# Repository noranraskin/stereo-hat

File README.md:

# Smart Stereo

A small, power-efficient AirPlay 2 network amplifier. A custom stereo class-D amplifier HAT sits on a Radxa Zero 3E running NixOS and `shairport-sync`, so any Apple device (or anything that speaks AirPlay 2) can stream straight to a pair of passive speakers over Ethernet.

## How it works

```
 iPhone / Mac ──AirPlay 2──▶ Ethernet ──▶ Radxa Zero 3E (NixOS, shairport-sync)
                                              │  I2S (pins 12, 35, 38, 40)
                                              │  I2C (pins 3, 5)
                                              ▼
 12–24 V DC ──▶ HAT ──▶ TPS54232 buck ──5 V──▶ SBC (via header pins 2/4)
                 │                      SBC 3.3 V ──▶ TAS5756M logic
                 └──────────── VIN ───▶ TAS5756M power stage ──▶ L / R speakers
```

- **SBC:** [Radxa Zero 3E](https://radxa.com/products/zeros/zero3e/). Small, low power, and has wired Ethernet. Any SBC with a Raspberry Pi-style 40-pin header and an I2S interface on the standard pins should work.
- **Amplifier:** TI [TAS5756M](https://www.ti.com/product/TAS5756M), a stereo I2S-input class-D amp with a built-in DAC and DSP. It receives audio over I2S and is configured over I2C.
- **Power:** one 12–24 V DC input feeds the amplifier directly. A TI [TPS54232](https://www.ti.com/product/TPS54232) buck converter makes 5 V for the SBC, so you need only one power supply. The 3.3 V for the amplifier's logic comes back from the SBC's own regulator.
- **Software:** NixOS, configured declaratively, so the same config can be copied to any number of speakers. `shairport-sync` is built with AirPlay 2 support, and `nqptp` handles AirPlay 2 timing.

The HAT is pin-compatible with the [HiFiBerry Amp2](https://www.hifiberry.com/shop/boards/hifiberry-amp2/), so it also works on a Raspberry Pi with the HiFiBerry drivers.

> [!IMPORTANT] 
> **!!IMPORTANT!! USING A SELF ASSEMBLED HAT WITH A RADXA AND NIXOS IS SOMEWHAT UNCONVENTIONAL. IF YOU USE ANY OTHER SETUP I CANNOT OFFER SUPPORT. THIS IS A HOBBY PROJECT, NOT A PRODUCT.**

## Repository layout

| Path | What it is |
| --- | --- |
| `kicad/` | KiCad 10 project for the HAT: schematics, PCB, custom symbols, footprints and 3D models |
| `kicad/bom/ibom.html` | Interactive BOM. Open it in a browser while placing parts |
| `kicad/datasheets/` | Datasheets for the TAS5756M and TPS54232 |
| `kicad/fabrication-toolkit-options.json` | Settings for the KiCad Fabrication Toolkit plugin (Gerbers, BOM, placement files) |
| `nix/configuration.nix` | Base NixOS system config |
| `nix/audio-hat.nix` | Device tree overlay that enables I2S, I2C and the TAS5756M sound card |
| `nix/airplay.nix` | `shairport-sync` (AirPlay 2), `nqptp` and Avahi |
| `imgs/` | Render and schematic exports used in this README |

## Hardware

### Schematics

| Sheet | |
| --- | --- |
| Top level / amplifier | [imgs/stereo.svg](imgs/stereo.svg) |
| 5 V power supply | [imgs/power.svg](imgs/power.svg) |
| SBC header and connectors | [imgs/io.svg](imgs/io.svg) |

### 40-pin header

Only these header pins are used. Everything else is left unconnected.

| Pin | Net | Purpose |
| --- | --- | --- |
| 1, 17 | 3.3V | Logic supply for the TAS5756M, from the SBC |
| 2, 4 | 5V | **Output** from the HAT's buck converter, powers the SBC |
| 3 | SDA | I2C data |
| 5 | SCL | I2C clock |
| 7 | SPK_MUTE | Amplifier mute (drive **high** to play) |
| 12 | SCLK | I2S bit clock |
| 35 | LRCK/FS | I2S word clock |
| 38 | ICSDOUT | I2S data from amp to SBC |
| 40 | ICSDIN | I2S data from SBC to amp |
| 6, 9, 14, 20, 25, 30, 34, 39 | GND | Ground |

### Building the board

1. Open `kicad/stereo.kicad_pro` in KiCad 10.
2. Generate fabrication files. The easiest way is the [Fabrication Toolkit](https://github.com/bennymeg/Fabrication-Toolkit) plugin (its settings are in `kicad/fabrication-toolkit-options.json`). It writes Gerbers, drill files, a BOM and a placement file to `kicad/production/`.
3. Order the PCB (2 layers, 1.6 mm), and optionally SMT assembly. Most passives are 0805 / 1210 with hand-solder pads, so hand assembly is practical too. The TAS5756M (TSSOP-48 with thermal pad) and TPS54232 (SO-8 PowerPAD) need their thermal pads soldered, so hot air or a reflow plate is recommended for those two.
4. Use `kicad/bom/ibom.html` to place the parts.

### Before first power-up

- Check for shorts between VIN, 5V, 3.3V and GND with a multimeter.
- Power the HAT alone first and confirm about 5 V on header pin 2 before plugging in the SBC.
- **Do not** power the SBC over USB-C while the HAT is powered. The HAT already feeds 5 V into the header.
- The speaker outputs are bridge-tied (BTL). Never connect a speaker's − terminal to ground, and never bridge the L and R − terminals.
- Use passive speakers rated for 4–8 Ω.

## Software (NixOS on the Radxa Zero 3E)

### 1. Install NixOS

Get a working aarch64 NixOS install booting on the Radxa Zero 3E with Ethernet up. Then generate the hardware config on the device:

```bash
sudo nixos-generate-config
```

This creates `/etc/nixos/hardware-configuration.nix`, which `configuration.nix` imports. It is specific to each device and not part of this repo.

### 2. Add the config from this repo

Copy the three files from `nix/` into `/etc/nixos/` on the device, then edit them:

- **`configuration.nix`:** add your SSH public key to `users.users.nixos.openssh.authorizedKeys.keys`, and set `networking.hostName` and `time.timeZone`.
- **`airplay.nix`:** change `"Name of Stereo"` to the name you want to see in the AirPlay menu. If you build several speakers, give each one a unique name and hostname.

Then build and switch:

```bash
sudo nixos-rebuild switch
```

Reboot once so the device tree overlay is loaded.

### What the config does

- **`audio-hat.nix`** adds a device tree overlay that:
  - enables the RK3566 `i2s3` controller on header pins 12 / 35 / 38 / 40;
  - enables `i2c3` on pins 3 / 5 and declares the TAS5756M at **both** possible I2C addresses (`0x4c` and `0x4d`), so the board works whatever the address strap is set to;
  - creates a sound card named `TAS5756M`, so the ALSA device is always `hw:TAS5756M`;
  - disables HDMI audio;
  - holds `GPIO3_C4` (header pin 7, `SPK_MUTE`) high, so the amplifier is unmuted at boot.

  It also loads the `snd_soc_pcm512x` driver, which supports the TAS5756M.
- **`airplay.nix`** builds `shairport-sync` with AirPlay 2 enabled, runs `nqptp` for AirPlay 2 timing, enables Avahi (mDNS) so the speaker shows up on your network, and trusts the `end0` Ethernet interface in the firewall.

### 3. Check it works

```bash
# The TAS5756M should be bound to its driver (shows "UU" at 4c or 4d)
i2cdetect -l
sudo i2cdetect -y <bus number of i2c3>

# The sound card should be listed
aplay -l

# Play a test tone on both channels (keep the volume low!)
speaker-test -D hw:TAS5756M -c 2 -t sine

# Follow the AirPlay service logs
journalctl -fu shairport-sync
```

The speaker should now show up in the AirPlay menu of any device on the same network.

## Using a Raspberry Pi instead

Since the HAT is pin-compatible with the HiFiBerry Amp2, a Raspberry Pi can use the HiFiBerry driver. In `/boot/firmware/config.txt`:

```
dtparam=audio=off
dtoverlay=hifiberry-dacplus
gpio=4=op,dh
```

`gpio=4=op,dh` drives header pin 7 (GPIO4) high to unmute the amplifier. On newer Raspberry Pi OS kernels the overlay may be named `hifiberry-dacplus-std`. Then install `shairport-sync` with AirPlay 2 support and point it at the `sndrpihifiberry` card.

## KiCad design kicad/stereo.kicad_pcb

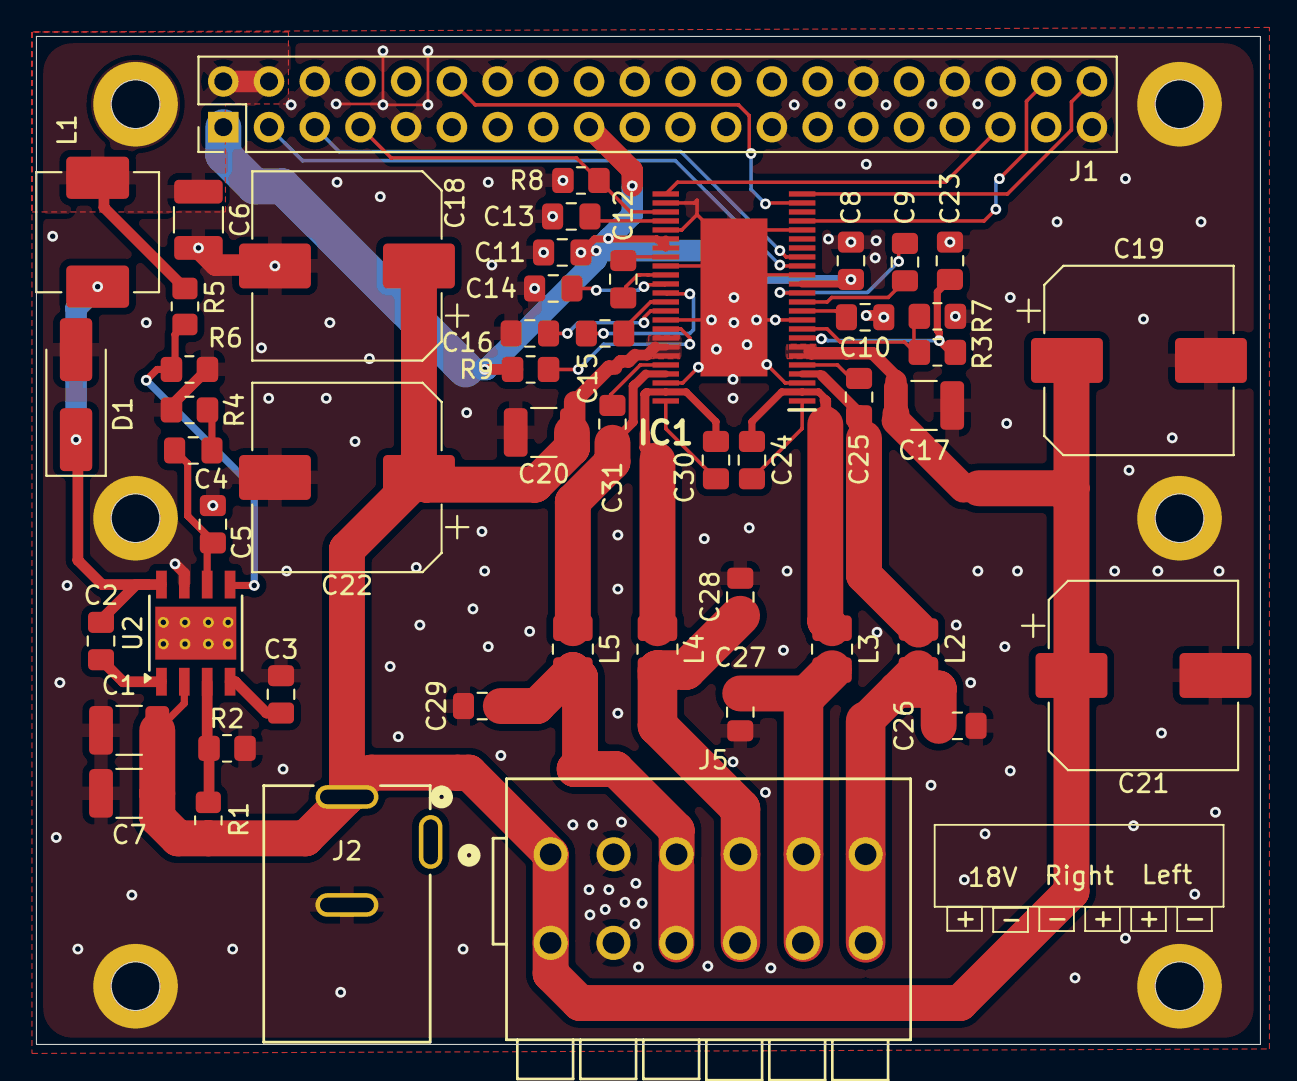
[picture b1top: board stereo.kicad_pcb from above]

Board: 2 copper layers, 68.0 x 56.0 mm, 51 parts (0 on the bottom side), 43 nets.

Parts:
C1, C7, C17, C20: 22µF; C_1210_3225Metric_Pad1.33x2.70mm_HandSolder
C2: 0.1µF; C_0805_2012Metric_Pad1.18x1.45mm_HandSolder
C3: 10nF; C_0805_2012Metric_Pad1.18x1.45mm_HandSolder
C4: 180pF; C_0805_2012Metric_Pad1.18x1.45mm_HandSolder
C5: 10pF; C_0805_2012Metric_Pad1.18x1.45mm_HandSolder
C6: 47µF; C_1210_3225Metric_Pad1.33x2.70mm_HandSolder
C8, C11, C12, C13, C14, C23: 1µF; C_0805_2012Metric_Pad1.18x1.45mm_HandSolder
C9, C10, C15, C16: 2.2µF; C_0805_2012Metric_Pad1.18x1.45mm_HandSolder
C18, C19, C21, C22: 220µF; CP_Elec_10x10
C24, C25, C30, C31: 0.22µF; C_0805_2012Metric_Pad1.18x1.45mm_HandSolder
C26, C27, C28, C29: 0.68µF; C_0805_2012Metric_Pad1.18x1.45mm_HandSolder
D1: B340; D_SMA_Handsoldering
IC1: TAS5756MDCAR; SOP50P810X120-49N
J1: Raspberry_Pi_4; PinHeader_2x20_P2.54mm_Vertical
J2: DC-005-A200; JACK_DC-005-A200_XNP
J5: 2601-1106; CONN3_2601-1106_WAG
L1: 6.8µH; L_Changjiang_FXL0630
L2: L; L_1008_2520Metric
L3, L4, L5: L; L_1008_2520Metric_Pad1.43x2.20mm_HandSolder
R1: 665k; R_0805_2012Metric_Pad1.20x1.40mm_HandSolder
R2: 84.5k; R_0805_2012Metric_Pad1.20x1.40mm_HandSolder
R3, R8, R9: 150k; R_0805_2012Metric_Pad1.20x1.40mm_HandSolder
R4: 75k; R_0805_2012Metric_Pad1.20x1.40mm_HandSolder
R5: 10.2k; R_0805_2012Metric_Pad1.20x1.40mm_HandSolder
R6: 1.96k; R_0805_2012Metric_Pad1.20x1.40mm_HandSolder
R7: 390k; R_0805_2012Metric_Pad1.20x1.40mm_HandSolder
U2: TPS54232DR; TI_SO-PowerPAD-8_ThermalVias

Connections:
3.3V: C8.1, C11.1, IC1.14 (AVDD), IC1.30 (DVDD), IC1.31 (CPVDD), J1.1 (3V3), J1.17 (3V3), R9.1
5V: C6.1, J1.2 (5V), J1.4 (5V), L1.2, R5.1
GND: C1.2, C3.2, C5.2, C6.2, C7.2, C8.2, C10.1, C11.2, C13.2, C14.2, C16.2, C17.2, C18.2, C19.2, C20.2, C21.2, C22.2, C23.2, C26.2, C27.2, C28.2, C29.2, D1.2 (A), IC1.3 (PGND_1), IC1.10 (AGND_1), IC1.15 (AGND_2), IC1.20 (ADR1), IC1.26 (ADR0), IC1.29 (DGND), IC1.33 (GND), IC1.39 (PGND_2), IC1.46 (PGND_3), IC1.49 (EP), J1.6 (GND), J1.9 (GND), J1.14 (GND), J1.20 (GND), J1.25 (GND), J1.30 (GND), J1.34 (GND), J1.39 (GND), J2.2, J5.2, R2.2, R4.2, R6.2, R7.1, R8.2, U2.7 (GND)
ICSDIN: IC1.24 (SDIN), J1.40 (GPIO21/SPI1_SCLK/PCM_DOUT)
ICSDOUT: IC1.21 (GPIO2), J1.38 (GPIO20/SPI1_MOSI/PCM_DIN/PWM1)
LRCK/FS: IC1.25 (LRCK/FS), J1.35 (GPIO19/SPI1_MISO/PCM_FS)
unnamed: C4.2, R4.1
unnamed: C2.2, D1.1 (K), L1.1, U2.8 (PH)
unnamed: C25.2, IC1.5 (BSTRPA+)
unnamed: C24.2, IC1.1 (BSTRPA-)
unnamed: C31.1, IC1.44 (BSTRPB+)
unnamed: C30.1, IC1.48 (BSTRPB-)
unnamed: C12.2, IC1.34 (CN)
unnamed: C12.1, IC1.32 (CP)
unnamed: C14.1, IC1.35 (CPVSS)
unnamed: C9.2, IC1.13 (DAC_OUTA)
unnamed: C15.1, IC1.36 (DAC_OUTB)
unnamed: C13.1, IC1.28 (DVDD_REG)
unnamed: C23.1, IC1.8 (GVDD_REG), R3.2
unnamed: IC1.9 (SPK_GAIN/FREQ), R3.1, R7.2
unnamed: C9.1, IC1.12 (SPK_INA+)
unnamed: C10.2, IC1.11 (SPK_INA-)
unnamed: C15.2, IC1.37 (SPK_INB+)
unnamed: C16.1, IC1.38 (SPK_INB-)
unnamed: C25.1, IC1.4 (SPK_OUTA+), L2.1
unnamed: C24.1, IC1.2 (SPK_OUTA-), L3.1
unnamed: C31.2, IC1.45 (SPK_OUTB+), L5.1
unnamed: C30.2, IC1.47 (SPK_OUTB-), L4.1
unnamed: C2.1, U2.1 (BOOT)
unnamed: C4.1, C5.1, U2.6 (COMP)
unnamed: R1.2, R2.1, U2.3 (EN)
unnamed: C3.1, U2.4 (SS)
unnamed: R5.2, R6.1, U2.5 (VSENSE)
OUTA+: C26.1, J5.6, L2.2
OUTA-: C27.1, J5.5, L3.2
OUTB+: C29.1, J5.3, L5.2
OUTB-: C28.1, J5.4, L4.2
SCL: IC1.17 (SCL), J1.5 (SCL_I2C1/GPIO03)
SCLK: IC1.23 (SCLK), J1.12 (GPIO18/SPI1_~CE0/PCM_CLK/PWM0)
SDA: IC1.16 (SDA), J1.3 (SDA_I2C1/GPIO02)
SPK_FAULT: IC1.40 (~SPK_FAULT), R9.2
SPK_MUTE: IC1.27 (~SPK_MUTE), J1.7 (GPCLK0/GPIO04), R8.1
VIN: C1.1, C7.1, C17.1, C18.1, C19.1, C20.1, C21.1, C22.1, IC1.6 (PVDD_1), IC1.7 (PVDD_2), IC1.41 (PVDD_3), IC1.42 (PVDD_4), IC1.43 (PVDD_5), J2.1, J5.1, R1.1, U2.2 (VIN)
